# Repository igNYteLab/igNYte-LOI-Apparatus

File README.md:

# igNYte LOI Apparatus

Monorepo for the IgNYte Lab limiting oxygen index (LOI) test bench. This
repository combines the embedded apparatus work and the operator web
application into one project while preserving the commit history of the original
repositories.

The apparatus is a custom LOI test bench inspired by ISO 4589-2 / ASTM D2863
workflows. It includes ESP32-P4 firmware, electronics documentation, validation
notes, serial control tools, camera-tracking prototypes, and a Next.js dashboard
for monitoring and recording tests.

## Repository Layout

```text
igNYte-LOI-Apparatus/,
  embedded/   Firmware, hardware files, validation docs, and apparatus tools
  example/    Example exported test runs and post-processing artifacts
  mechanical/ Mechanical design docs, CAD exports, assembly notes, and BOMs
  webapp/     Next.js operator dashboard and test-monitoring application
```

## What Is Included

| Path | Contents |
| --- | --- |
| [`embedded/`](embedded/) | Former `IgNYte-FPA` repository. Contains the ESP32-P4 sensor-hub firmware, KiCad hardware files, firmware protocol docs, validation notes, OpenCV prototype, and apparatus helper tools. |
| [`example/`](example/) | Example exported test runs from the apparatus web app, including run metadata, sensor telemetry, camera videos, exported frames, and vision-tracking outputs. |
| [`mechanical/`](mechanical/) | Mechanical documentation and future design artifacts for the chamber, frame, sample holder, camera stage, motor mount, assembly process, and mechanical bill of materials. |
| [`webapp/`](webapp/) | Former `ignyte` repository. Contains the production web dashboard for Web Serial device control, live telemetry, session recording, camera/vision controls, Firebase auth, and user management. |

## Embedded Apparatus

Start here for firmware, hardware, and apparatus-level documentation:

- [Embedded README](embedded/README.md)
- [Firmware README](embedded/firmware/p4-sensor-hub-arduino/README.md)
- [Serial protocol](embedded/docs/firmware-serial-protocol.md)
- [Hardware overview](embedded/hardware/README.md)
- [Hardware errata](embedded/hardware/errata.md)
- [Operator demo flow](embedded/docs/operator-demo-flow.md)
- [Final validation notes](embedded/docs/final-validation.md)
- [Future work](embedded/docs/futurework.md)

Active firmware path:

```text
embedded/firmware/p4-sensor-hub-arduino/
```

Common firmware commands:

```powershell
pio run -d embedded/firmware/p4-sensor-hub-arduino
pio test -d embedded/firmware/p4-sensor-hub-arduino -e native
pio run -d embedded/firmware/p4-sensor-hub-arduino -e esp32-p4-motor-debug
```

The firmware communicates over USB serial at `115200` baud using
newline-delimited JSON. Commands and telemetry are documented in
[`embedded/docs/firmware-serial-protocol.md`](embedded/docs/firmware-serial-protocol.md).

## System Block Diagram

The system block diagram shows how the physical apparatus, `motherV1`
electronics, ESP32-P4 firmware, host web app, camera/vision tools, and exported
test data fit together.

## Mechanical

Use [`mechanical/`](mechanical/) for documentation and artifacts tied to the
physical apparatus: CAD files, exported drawings, assembly notes, mechanical
BOMs, camera-stage hardware, chamber/frame design, sample-holder details, travel
limits, alignment notes, and build photos.

Mechanical changes can affect firmware constants, camera tracking behavior, and
validation results. When the physical stage, chamber, camera payload, or motion
hardware changes, update the relevant embedded validation and future-work docs.

## Web Application

Start here for the dashboard and operator UI:

- [Web app README](webapp/README.md)
- [Firmware protocol parser](webapp/lib/firmware.ts)
- [Firestore security rules](webapp/firestore.rules)
- [Sample-test database schema](webapp/db/schema.sql)
- [Vision controller code](webapp/lib/vision/)

The web app provides:

- Web Serial connection to the ESP32-P4 apparatus
- Live sensor telemetry and rolling charts
- Motor, flow-controller, and sensor command controls
- Safety-gated test recording
- RGB camera capture and OpenCV flame tracking
- Firebase authentication and user management
- Exported test archives for post-processing

Run the web app locally:

```powershell
cd webapp
npm install
npm run dev
```

Open <http://localhost:3000> in Chrome or Edge. Web Serial requires a Chromium
browser served from `localhost` or HTTPS.

Create `webapp/.env.local` before running against Firebase-backed features. The
web app expects `NEXT_PUBLIC_FIREBASE_*` values and optional camera stream URLs;
see [`webapp/README.md`](webapp/README.md) for the current environment details.

## Example Test Runs

Use [`example/`](example/) for exported sample runs from the full apparatus
workflow. These examples show the output shape produced by the web app after a
recorded test, including:

- run metadata and timing
- firmware sensor telemetry
- RGB and HSI/source video recordings
- exported still frames for frame-by-frame analysis
- flame-tracking overlay video and vision metrics
- sensor-sample-to-frame associations for easier post-processing

The included Kitchen Towel example,
[`example/20260724-143958-LOI-1/`](example/20260724-143958-LOI-1/), documents a
34.3 second test export with 525 sensor samples, 172 exported frames, and 213
vision metric samples.

## Monorepo History

This repository was assembled with `git subtree` so that both source histories
remain visible in the combined repository.

Original sources:

- `embedded/`: <https://github.com/andre-llaneta/IgNYte-FPA>
- `webapp/`: <https://github.com/ikasturirangan/ignyte>

Useful history commands:

```powershell
git log --all --graph --oneline --decorate --date-order
git log -- embedded
git log -- webapp
```

## Syncing Source Repositories

While the original repositories remain active, sync their latest changes into
this monorepo with the GitHub Actions workflow:

1. Open the repository on GitHub.
2. Go to **Actions**.
3. Select **Sync Source Repos**.
4. Click **Run workflow**.
5. Choose the `main` branch.
6. Click **Run workflow** again to start the sync.

The workflow also runs automatically on its configured schedule. It pulls:

- `embedded/` from `andre-llaneta/IgNYte-FPA`
- `webapp/` from `ikasturirangan/ignyte`

Do not use `--squash` if the goal is to preserve the full upstream commit
history.

## Development Notes

- Keep apparatus firmware and hardware work under `embedded/`.
- Keep exported demonstration runs and post-processing examples under
  `example/`.
- Keep mechanical design files, CAD exports, assembly notes, and mechanical BOMs
  under `mechanical/`.
- Keep dashboard, auth, database, and browser-side control work under `webapp/`.
- Update root-level documentation when behavior crosses both parts of the
  system.
- Keep local secrets in ignored `.env.local` files. Do not commit credentials,
  private keys, Firebase service-account files, or machine-specific build
  artifacts.
- Generated directories such as `node_modules/`, `.next/`, build outputs, and
  cache files should stay out of Git.

## Project Status

The combined repository is intended to be the long-term home for the full IgNYte
LOI apparatus stack. The embedded subtree documents the apparatus firmware,
hardware bring-up, validation history, and remaining integration work. The web
app subtree contains the operator-facing dashboard for connecting to the board,
streaming telemetry, controlling the test bench, recording sessions, and
exporting test data.

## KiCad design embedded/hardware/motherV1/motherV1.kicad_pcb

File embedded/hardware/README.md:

<!--
Primary author: Will Andre Pasimio Llaneta (wpl5304)
GitHub: https://github.com/andre-llaneta
Project: IgNYte-FPA
Context: NYU Tandon IgNYte Lab fire propagation apparatus internship work.
-->

# motherV1

`motherV1` is a fabricated and tested custom DAQ/interface motherboard for the IgNYte-FPA ESP32-P4 sensor hub. It consolidates the apparatus support electronics onto one PCB, mounting the FireBeetle 2 ESP32-P4, sensor breakout interfaces, TMC2209 stepper-driver interface, RS232 flow-controller interfaces, and 20 V / 5 V / 3.3 V power distribution used for fire-propagation apparatus bring-up and firmware integration.

The board is intended to reduce loose wiring during apparatus bring-up by collecting the major support electronics on one PCB:

- DFRobot FireBeetle 2 ESP32-P4 controller interface
- Adafruit TMC2209 stepper motor driver interface
- Adafruit MCP23017 I/O expander
- 4 Adafruit MAX31856 thermocouple interfaces
- Adafruit SHT45, Adafruit BME688, and DFRobot SEN0496 I2C sensor interfaces
- SPI and analog sensor expansion
- Omron D6F analog flow sensor support
- Adafruit RS232 Pal interfaces for flow-controller UART level shifting
- Motor DIAG, INDEX, and endstop-related signals
- USB-C power input
- MPM3610 buck converter
- TPS62827 buck converter
- Power distribution for the sensor hub peripherals

## External Boards And Modules

The current board was designed around these external boards/modules and sensor breakouts. Verify exact part numbers against the BOM and physical hardware before ordering replacements.

| Function | Part / module | Link |
| --- | --- | --- |
| Main MCU | DFRobot FireBeetle 2 ESP32-P4 AI Vision Board | [DFRobot product page](https://www.dfrobot.com/product-2915.html) / [DFRobot wiki](https://wiki.dfrobot.com/dfr1172/) |
| Stepper driver | Adafruit TMC2209 Stepper Motor Driver Breakout Board | [Adafruit product 6121](https://www.adafruit.com/product/6121) |
| Thermocouple interface | Adafruit Universal Thermocouple Amplifier MAX31856 Breakout | [Adafruit product 3263](https://www.adafruit.com/product/3263) |
| Temperature/RH | Adafruit Sensirion SHT45 Precision Temperature & Humidity Sensor | [Adafruit product 5665](https://www.adafruit.com/product/5665) |
| Environment / gas | Adafruit BME688 Temperature, Humidity, Pressure and Gas Sensor | [Adafruit product 5046](https://www.adafruit.com/product/5046) |
| Oxygen | DFRobot Gravity SEN0496 Electrochemical Oxygen / O2 Sensor | [DFRobot product page](https://www.dfrobot.com/product-2569.html) / [DFRobot wiki](https://wiki.dfrobot.com/sen0496/) |
| I/O expansion | Adafruit MCP23017 I2C GPIO Expander Breakout | [Adafruit product 5346](https://www.adafruit.com/product/5346) |
| RS232 level shifting | Adafruit RS232 Pal MAX3232E | [Adafruit product 5987](https://www.adafruit.com/product/5987) |
| 5 V buck converter | Adafruit MPM3610 5V Buck Converter Breakout | [Adafruit product 4739](https://www.adafruit.com/product/4739) |
| 3.3 V buck converter IC | Texas Instruments TPS62827 | [TI product page](https://www.ti.com/product/TPS62827) |
| Analog flow velocity sensor | Omron D6F series / D6F-V03A1 | [Omron D6F series](https://components.omron.com/us-en/products/sensors/D6F) |

## Directory Layout

```text
hardware/
  README.md
  errata.md
  motherV1/
    motherV1.kicad_pro
    motherV1.kicad_sch
    motherV1.kicad_pcb
    motherv1-schematic.pdf
    jlcpcb/
      motherV1.zip
      bom.csv
      positions.csv
      designators.csv
      netlist.ipc
```

## Design Files

The KiCad source files for the board are stored in `hardware/motherV1/`.

- `motherV1.kicad_pro`: KiCad project file
- `motherV1.kicad_sch`: schematic source
- `motherV1.kicad_pcb`: PCB layout source
- `motherv1-schematic.pdf`: exported schematic PDF for quick review

The `hardware/motherV1/jlcpcb/` directory contains manufacturing/export files for JLCPCB, including the Gerber archive, BOM, component placement data, designators, and IPC netlist.

## Board Status

`motherV1` has been fabricated and tested. The board is usable for current bring-up and firmware integration work, but it has known revision notes that should be addressed before a future hardware revision.

See [errata.md](./errata.md) for confirmed hardware issues and next-revision recommendations.

## Validation Summary

| Subsystem | Status | Evidence |
| --- | --- | --- |
| 20 V input | Validated | Measured voltage/current |
| 5 V buck | Validated | No-load/load voltage |
| 3.3 V buck | Validated | No-load/load voltage |
| FireBeetle headers | Usable with errata | Footprint offset noted |
| I2C sensors | Validated | Scan + telemetry |
| Thermocouples | Validated | MAX31856 telemetry |
| TMC2209 | Validated with bodge | UART/status/motion |
| Endstop | Works, needs connector | Errata |
| Flow RS232 | Pending controllers | Planned test |

## Thermocouple Channel Mapping

The current firmware labels the four installed MAX31856 thermocouple channels by their chip-select GPIOs. The confirmed physical thermocouple order is:

| Physical thermocouple order | Firmware sensor name | GPIO / CS |
| ---: | --- | ---: |
| 1 | `tc1` | 21 |
| 2 | `tc2` | 36 |
| 3 | `tc3` | 35 |
| 4 | `tc4` | 20 |

The remaining SPI chip-selects, GPIO `34` and GPIO `31`, are reserved for future offboard SPI devices.

## Known Errata Summary

The current hardware errata includes:

- Missing dedicated motor endstop connector
- TMC2209 UART RX path requiring a 1 kOhm series resistor / bodge routing
- Insufficient convenient ground access points for bring-up and probing
- FireBeetle 2 ESP32-P4 header footprint offset of approximately 1 mm

Refer to [errata.md](./errata.md) for the detailed impact and proposed fixes for each issue.

## Notes For Bring-Up

- Before applying power, verify every socketed module and breakout board is seated in the correct header, correct orientation, and correct pin alignment. The board uses female headers for several modules, so it is possible to insert a module into the wrong position or offset it by one pin without noticing. A one-pin offset can connect supply voltage to the wrong module pin and permanently damage hardware.
- Keep the motor driver and motor power available during firmware boot when testing motor configuration. If the driver is unpowered during initialization, configuration commands such as microstep setup may not take effect and the driver can remain at its default settings.
- Treat the JLCPCB export folder as a snapshot of the current fabricated revision. Regenerate manufacturing files from KiCad before ordering a revised board.
- Do not delete or ignore the errata when using this revision; several issues affect motor bring-up, wiring reliability, and next-board layout changes.

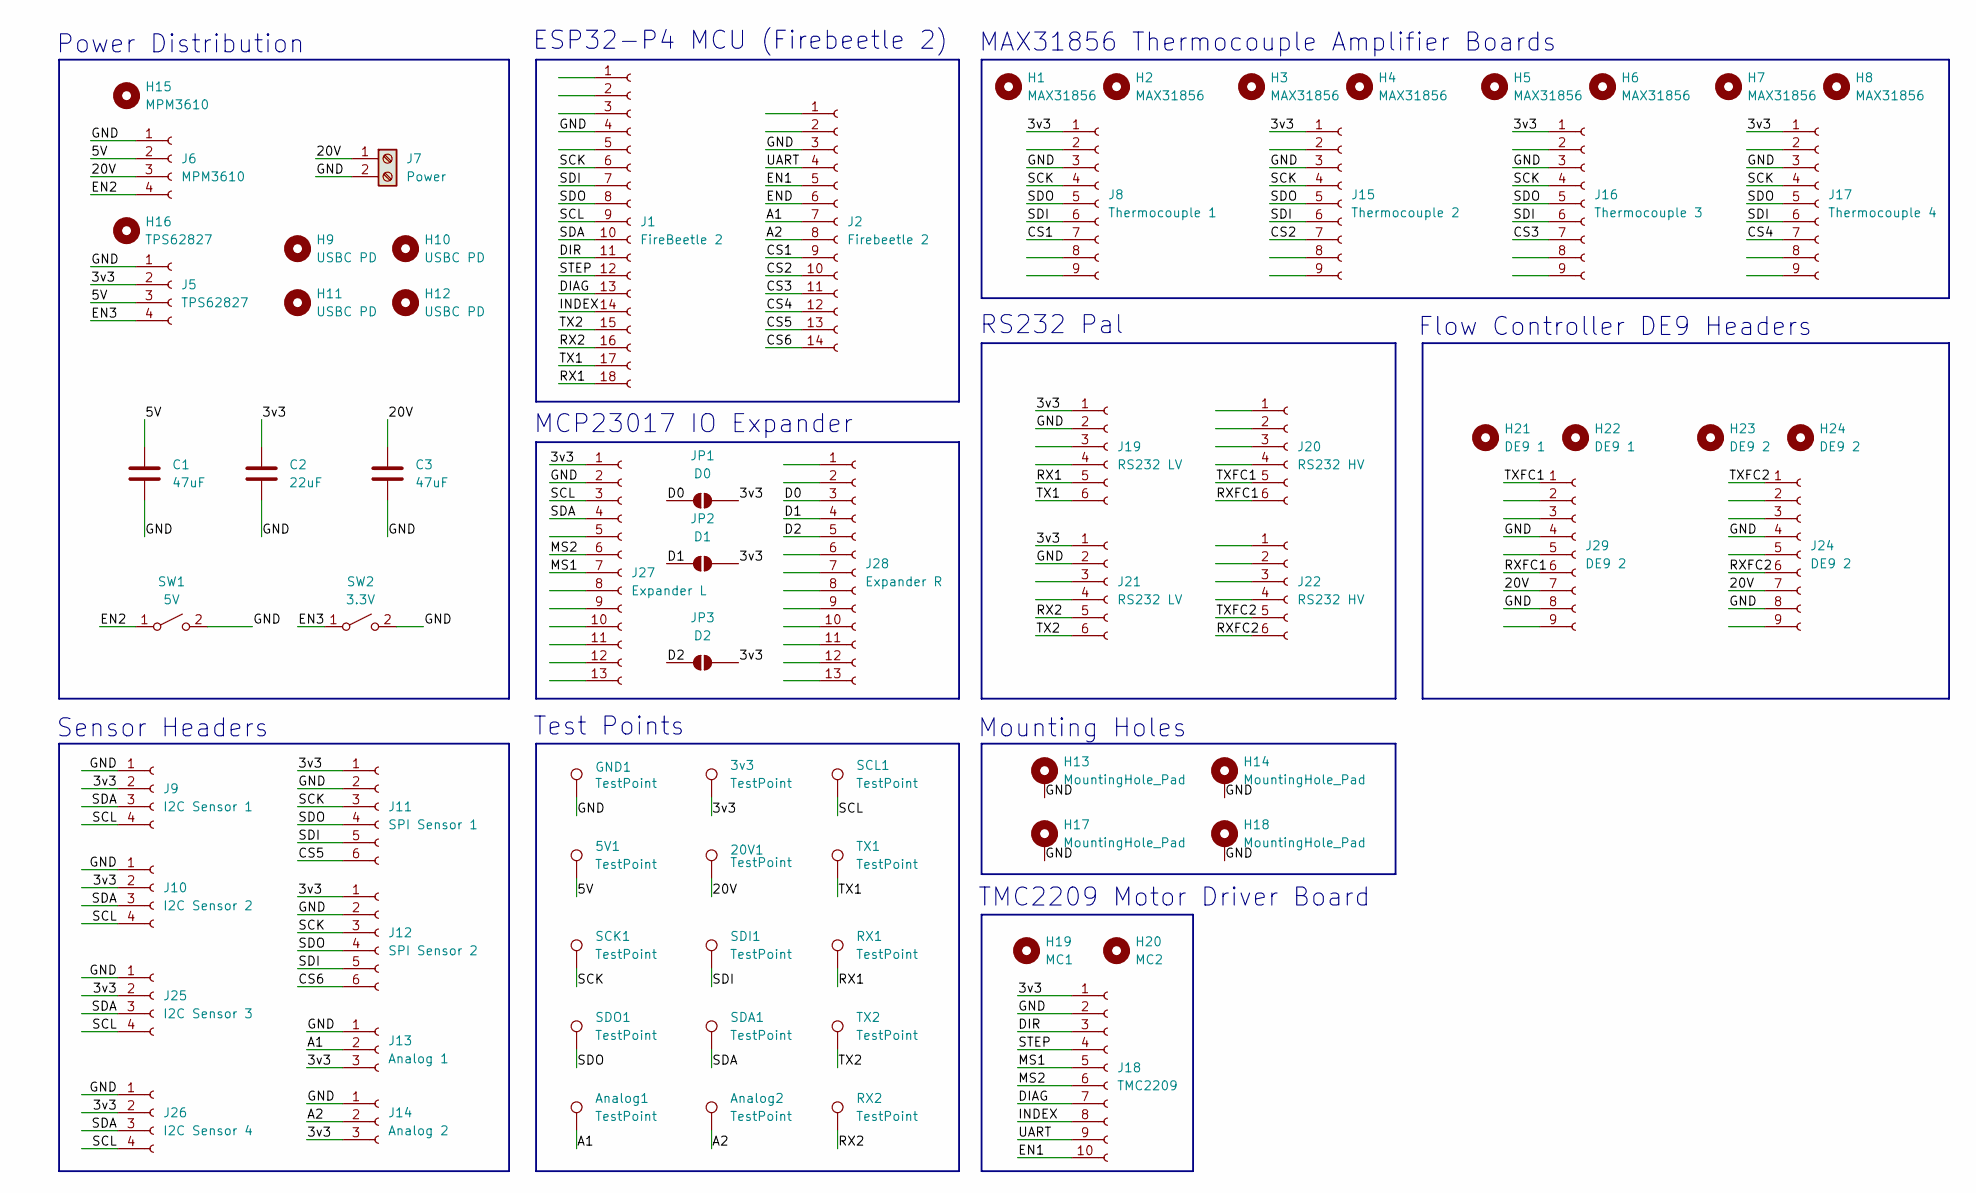
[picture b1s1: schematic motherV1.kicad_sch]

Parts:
3v3, 5V1, 20V1: TestPoint; TestPoint_Pad_D1.5mm
Analog1, Analog2: TestPoint; TestPoint_Pad_D1.5mm
C1, C3: 47uF; C_1206_3216Metric; LCSC PN C96123
C2: 22uF; C_1206_3216Metric; LCSC PN C12891
GND1: TestPoint; TestPoint_Pad_D1.5mm
H1, H2, H3, H4, H5, H6, H7, H8: MAX31856; MountingHole_3.2mm_M3
H9, H10, H11, H12: USBC PD; MountingHole_3.2mm_M3
H13, H14, H17, H18: MountingHole_Pad; MountingHole_3.2mm_M3_DIN965_Pad
H15: MPM3610; MountingHole_3.2mm_M3
H16: TPS62827; MountingHole_3.2mm_M3
H19: MC1; MountingHole_3.2mm_M3
H20: MC2; MountingHole_3.2mm_M3
H21, H22: DE9 1; MountingHole_3.2mm_M3
H23, H24: DE9 2; MountingHole_3.2mm_M3
J1: FireBeetle 2; PinSocket_1x18_P2.54mm_Vertical; LCSC PN C22373904
J2: Firebeetle 2; PinSocket_1x14_P2.54mm_Vertical; LCSC PN C22373900
J5: TPS62827; PinSocket_1x04_P2.54mm_Vertical; LCSC PN C22373890
J6: MPM3610; PinSocket_1x04_P2.54mm_Vertical; LCSC PN C22373890
J7: Power; TerminalBlock_Phoenix_MKDS-3-2-5.08_1x02_P5.08mm_Horizontal; LCSC PN C89120
J8: Thermocouple 1; PinSocket_1x09_P2.54mm_Vertical; LCSC PN C22373895
J9: I2C Sensor 1; JST_SH_SM04B-SRSS-TB_1x04-1MP_P1.00mm_Horizontal; LCSC PN C160404
J10: I2C Sensor 2; JST_SH_SM04B-SRSS-TB_1x04-1MP_P1.00mm_Horizontal; LCSC PN C160404
J11: SPI Sensor 1; JST_SH_SM06B-SRSS-TB_1x06-1MP_P1.00mm_Horizontal; LCSC PN C160405
J12: SPI Sensor 2; JST_SH_SM06B-SRSS-TB_1x06-1MP_P1.00mm_Horizontal; LCSC PN C160405
J13: Analog 1; JST_SH_SM03B-SRSS-TB_1x03-1MP_P1.00mm_Horizontal; LCSC PN C160403
J14: Analog 2; JST_SH_SM03B-SRSS-TB_1x03-1MP_P1.00mm_Horizontal; LCSC PN C160403
J15: Thermocouple 2; PinSocket_1x09_P2.54mm_Vertical; LCSC PN C22373895
J16: Thermocouple 3; PinSocket_1x09_P2.54mm_Vertical; LCSC PN C22373895
J17: Thermocouple 4; PinSocket_1x09_P2.54mm_Vertical; LCSC PN C22373895
J18: TMC2209; PinSocket_1x10_P2.54mm_Vertical; LCSC PN C22373896
J19, J21: RS232 LV; PinSocket_1x06_P2.54mm_Vertical; LCSC PN C22373892
J20, J22: RS232 HV; PinSocket_1x06_P2.54mm_Vertical; LCSC PN C22373892
J24, J29: DE9 2; PinSocket_1x09_P2.54mm_Vertical; LCSC PN C22373895
J25: I2C Sensor 3; JST_SH_SM04B-SRSS-TB_1x04-1MP_P1.00mm_Horizontal; LCSC PN C160404
J26: I2C Sensor 4; JST_SH_SM04B-SRSS-TB_1x04-1MP_P1.00mm_Horizontal; LCSC PN C160404
J27: Expander L; PinSocket_1x13_P2.54mm_Vertical; LCSC PN C22373899
J28: Expander R; PinSocket_1x13_P2.54mm_Vertical; LCSC PN C22373899
JP1: D0; SolderJumper-2_P1.3mm_Open_Pad1.0x1.5mm
JP2: D1; SolderJumper-2_P1.3mm_Open_Pad1.0x1.5mm
JP3: D2; SolderJumper-2_P1.3mm_Open_Pad1.0x1.5mm
RX1, RX2: TestPoint; TestPoint_Pad_D1.5mm
SCK1: TestPoint; TestPoint_Pad_D1.5mm
SCL1: TestPoint; TestPoint_Pad_D1.5mm
SDA1: TestPoint; TestPoint_Pad_D1.5mm
SDI1: TestPoint; TestPoint_Pad_D1.5mm
SDO1: TestPoint; TestPoint_Pad_D1.5mm
SW1: 5V; SW_SPDT_Shouhan_MSK12C02; LCSC PN C431540
SW2: 3.3V; SW_SPDT_Shouhan_MSK12C02; LCSC PN C431540
TX1, TX2: TestPoint; TestPoint_Pad_D1.5mm

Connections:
/3v3: 3v3.1 (1_1), C2.1, J5.2, J8.1, J9.2, J10.2, J11.1, J12.1, J13.3, J14.3, J15.1, J16.1, J17.1, J18.1, J19.1, J21.1, J25.2, J26.2, J27.1, JP1.2 (B), JP2.2 (B), JP3.2 (B)
/5V: 5V1.1 (1_1), C1.1, J5.3, J6.2
/20V: 20V1.1 (1_1), C3.1, J6.3, J7.1, J24.7, J29.7
/A1: Analog1.1 (1_1), J2.7, J13.2
/A2: Analog2.1 (1_1), J2.8, J14.2
/CS1: J2.9, J8.7
/CS2: J2.10, J15.7
/CS3: J2.11, J16.7
/CS4: J2.12, J17.7
/CS5: J2.13, J11.6
/CS6: J2.14, J12.6
/D0: J28.3, JP1.1 (A)
/D1: J28.4, JP2.1 (A)
/D2: J28.5, JP3.1 (A)
/DIAG: J1.13, J18.7
/DIR: J1.11, J18.3
/EN1: J2.5, J18.10
/EN2: J6.4, SW1.1 (A)
/EN3: J5.4, SW2.1 (A)
/END: J2.6
/GND: C1.2, C2.2, C3.2, GND1.1 (1_1), H13.1 (1_1), H14.1 (1_1), H17.1 (1_1), H18.1 (1_1), J1.4, J2.3, J5.1, J6.1, J7.2, J8.3, J9.1, J10.1, J11.2, J12.2, J13.1, J14.1, J15.3, J16.3, J17.3, J18.2, J19.2, J21.2, J24.4, J24.8, J25.1, J26.1, J27.2, J29.4, J29.8, SW1.2 (B), SW2.2 (B)
/INDEX: J1.14, J18.8
/MS1: J18.5, J27.7
/MS2: J18.6, J27.6
/RX1: J1.18, J19.5, RX1.1 (1_1)
/RX2: J1.16, J21.5, RX2.1 (1_1)
/RXFC1: J20.6, J29.6
/RXFC2: J22.6, J24.6
/SCK: J1.6, J8.4, J11.3, J12.3, J15.4, J16.4, J17.4, SCK1.1 (1_1)
/SCL: J1.9, J9.4, J10.4, J25.4, J26.4, J27.3, SCL1.1 (1_1)
/SDA: J1.10, J9.3, J10.3, J25.3, J26.3, J27.4, SDA1.1 (1_1)
/SDI: J1.7, J8.6, J11.5, J12.5, J15.6, J16.6, J17.6, SDI1.1 (1_1)
/SDO: J1.8, J8.5, J11.4, J12.4, J15.5, J16.5, J17.5, SDO1.1 (1_1)
/STEP: J1.12, J18.4
/TX1: J1.17, J19.6, TX1.1 (1_1)
/TX2: J1.15, J21.6, TX2.1 (1_1)
/TXFC1: J20.5, J29.1
/TXFC2: J22.5, J24.1
/UART: J2.4, J18.9

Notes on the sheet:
TMC2209 Motor Driver Board
Mounting Holes
ESP32-P4 MCU (Firebeetle 2)
MCP23017 IO Expander
Test Points
Power Distribution
MAX31856 Thermocouple Amplifier Boards
Flow Controller DE9 Headers
Sensor Headers
RS232 Pal

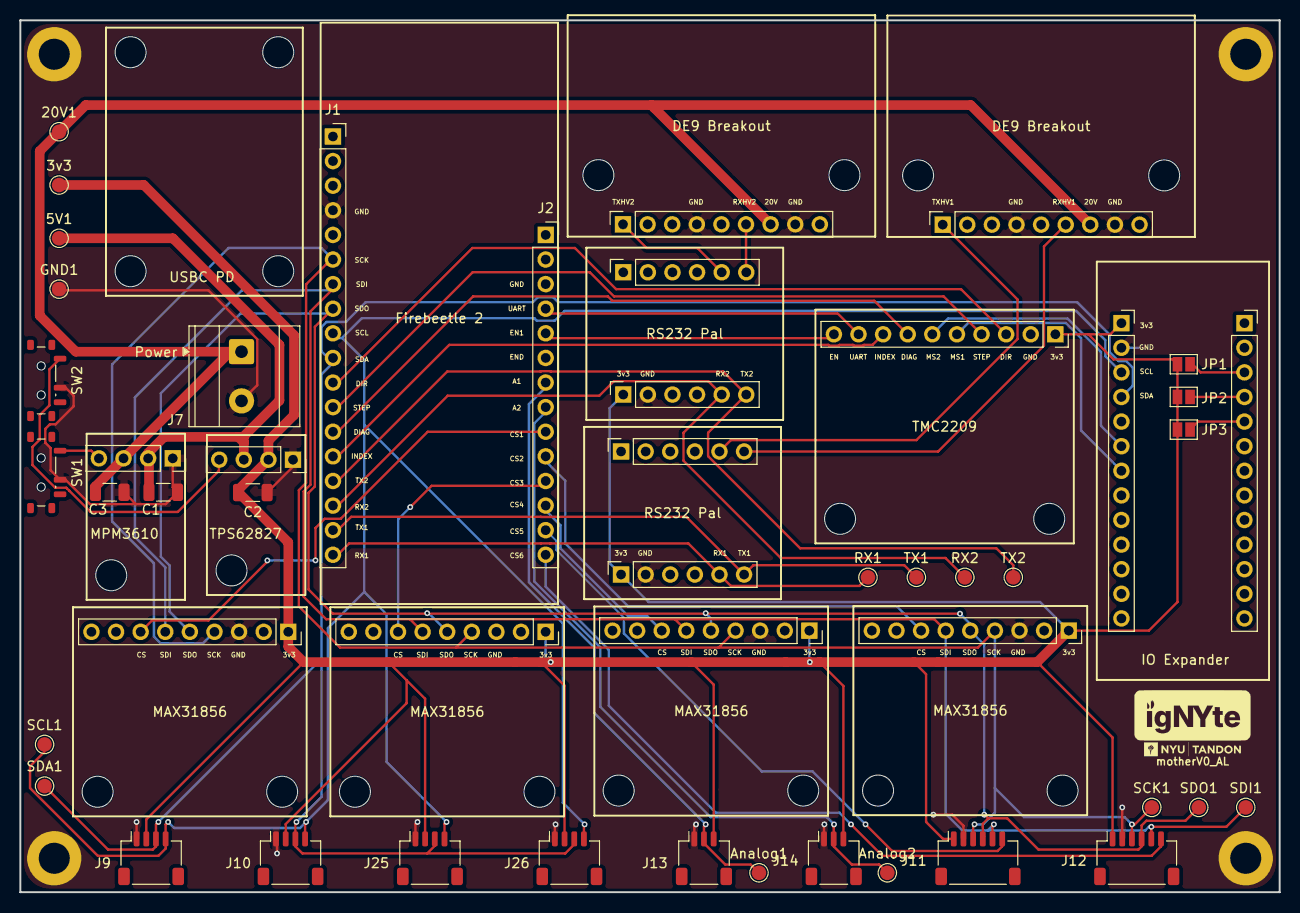
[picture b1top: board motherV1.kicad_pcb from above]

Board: 2 copper layers, 130.0 x 90.0 mm, 73 parts (0 on the bottom side), 38 nets.

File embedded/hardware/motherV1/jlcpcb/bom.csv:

Designator,Footprint,Quantity,Value,LCSC Part #
"C1, C3",1206,2,47uF,C96123
C2,1206,1,22uF,C12891
J1,PinSocket_1x18_P2.54mm_Vertical,1,FireBeetle 2,C22373904 
J10,JST_SH_SM04B-SRSS-TB_1x04-1MP_P1.00mm_Horizontal,1,I2C Sensor 2,C160404
J11,JST_SH_SM06B-SRSS-TB_1x06-1MP_P1.00mm_Horizontal,1,SPI Sensor 1,C160405
J12,JST_SH_SM06B-SRSS-TB_1x06-1MP_P1.00mm_Horizontal,1,SPI Sensor 2,C160405
J13,JST_SH_SM03B-SRSS-TB_1x03-1MP_P1.00mm_Horizontal,1,Analog 1,C160403
J14,JST_SH_SM03B-SRSS-TB_1x03-1MP_P1.00mm_Horizontal,1,Analog 2,C160403
J15,PinSocket_1x09_P2.54mm_Vertical,1,Thermocouple 2,C22373895
J16,PinSocket_1x09_P2.54mm_Vertical,1,Thermocouple 3,C22373895
J17,PinSocket_1x09_P2.54mm_Vertical,1,Thermocouple 4,C22373895
J18,PinSocket_1x10_P2.54mm_Vertical,1,TMC2209,C22373896
"J19, J21",PinSocket_1x06_P2.54mm_Vertical,2,RS232 LV,C22373892
J2,PinSocket_1x14_P2.54mm_Vertical,1,Firebeetle 2,C22373900
"J20, J22",PinSocket_1x06_P2.54mm_Vertical,2,RS232 HV,C22373892
"J24, J29",PinSocket_1x09_P2.54mm_Vertical,2,DE9 2,C22373895
J25,JST_SH_SM04B-SRSS-TB_1x04-1MP_P1.00mm_Horizontal,1,I2C Sensor 3,C160404
J26,JST_SH_SM04B-SRSS-TB_1x04-1MP_P1.00mm_Horizontal,1,I2C Sensor 4,C160404
J27,PinSocket_1x13_P2.54mm_Vertical,1,Expander L,C22373899
J28,PinSocket_1x13_P2.54mm_Vertical,1,Expander R,C22373899
J5,PinSocket_1x04_P2.54mm_Vertical,1,TPS62827,C22373890
J6,PinSocket_1x04_P2.54mm_Vertical,1,MPM3610,C22373890
J7,TerminalBlock_Phoenix_MKDS-3-2-5.08_1x02_P5.08mm_Horizontal,1,Power,C89120
J8,PinSocket_1x09_P2.54mm_Vertical,1,Thermocouple 1,C22373895
J9,JST_SH_SM04B-SRSS-TB_1x04-1MP_P1.00mm_Horizontal,1,I2C Sensor 1,C160404
SW1,SW_SPDT_Shouhan_MSK12C02,1,5V,C431540
SW2,SW_SPDT_Shouhan_MSK12C02,1,3.3V,C431540

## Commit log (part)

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2026-05-30 feat: initial commit
2026-06-08 added ReadMes
2026-06-09 added platformio bring up firmware, needs review
2026-06-10 docs: add project-context.md and workflow.md
2026-06-10 feat: add MCP23017 wrapper for motor microstep pins
    Configure MS1/MS2 from Config::kMicrosteps during boot. Set 1/16 microstepping by driving both MS pins high through the MCP23017. Document the expander behavior and remaining hardware verification ri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
2026-06-11 docs: add debug-log.md
2026-06-11 feat: queue motor commands through motor task
    Route motor commands through a FreeRTOS queue so motorTask owns MotorController state. Add MCP23017-backed microstep pin setup, centralize sensor rates in AppConfig, and update project docs with risk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
2026-06-12 docs: add hardware/errata.md
2026-06-15 fix: upd TMC2209 sense resistor value from 0.11 to 0.05
2026-06-17 docs: add serial-protocol.md
2026-06-17 docs: add header pin offset errata
2026-06-24 feat: add SEN0496 oxygen sensor support
    Add a local SEN0496 I2C oxygen sensor wrapper and instantiate it as o2 at the default 0x70 address.
    Update JSON command docs, serial protocol notes, project context, and change log for the oxygen sensor, current sensor task state, motor/StallGuard defaults, and hardware bring-up constraints.
    Document hardware errata for the endstop header requirement, Analog 1 TMC UART bodge, and TMC2209 UART RX routing through a 1 kOhm series resistor.
2026-06-24 fix: improve sensor sampling throughput
    Split sensor polling into fast I2C, BME688, and thermocouple tasks with bus mutexes.
    Run BME688 reads as async start/finish cycles so the gas-heater wait does not hold the I2C bus.
    Use continuous MAX31856 conversion mode to avoid blocking thermocouple one-shot conversions and update docs for the new task layout.
